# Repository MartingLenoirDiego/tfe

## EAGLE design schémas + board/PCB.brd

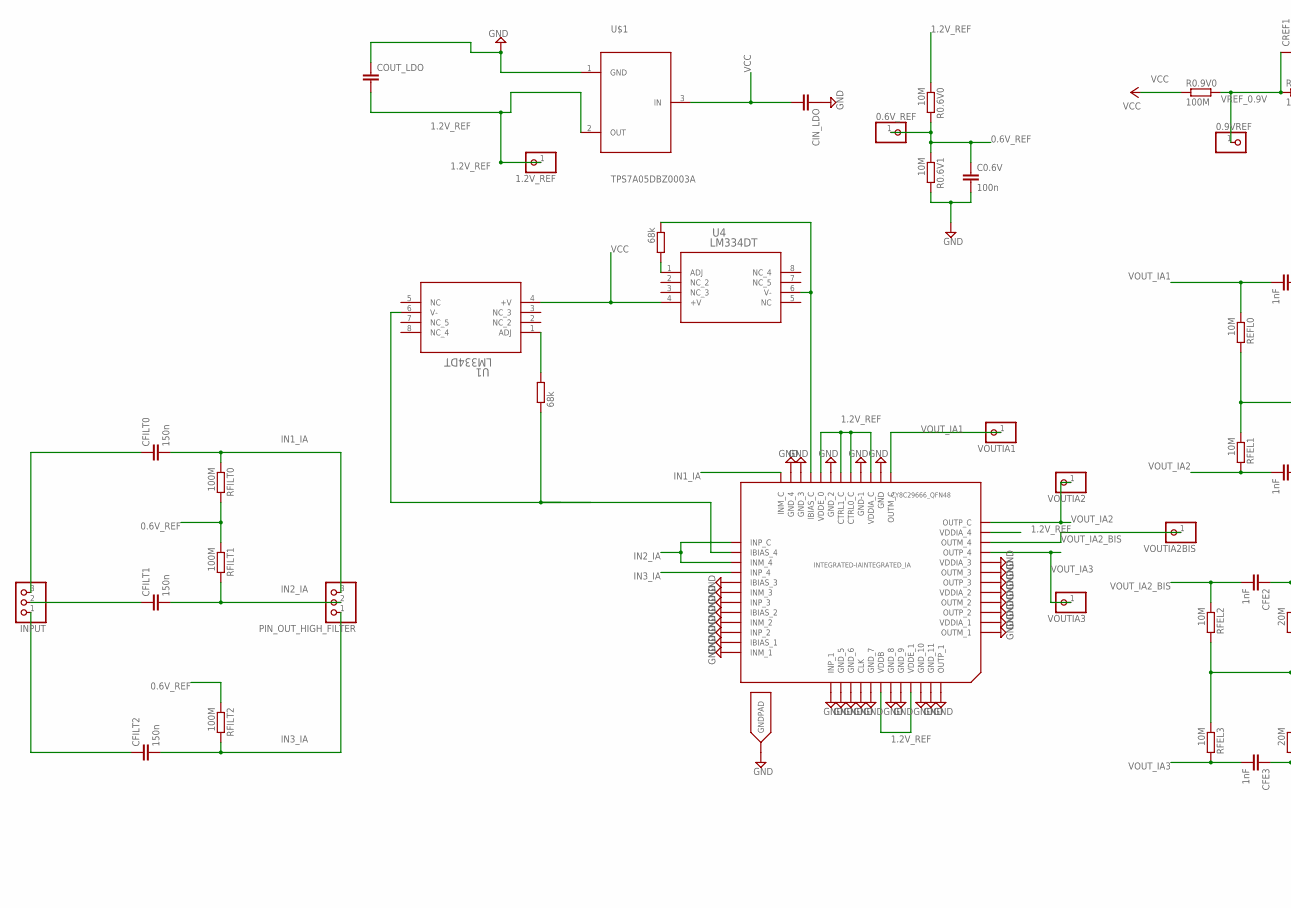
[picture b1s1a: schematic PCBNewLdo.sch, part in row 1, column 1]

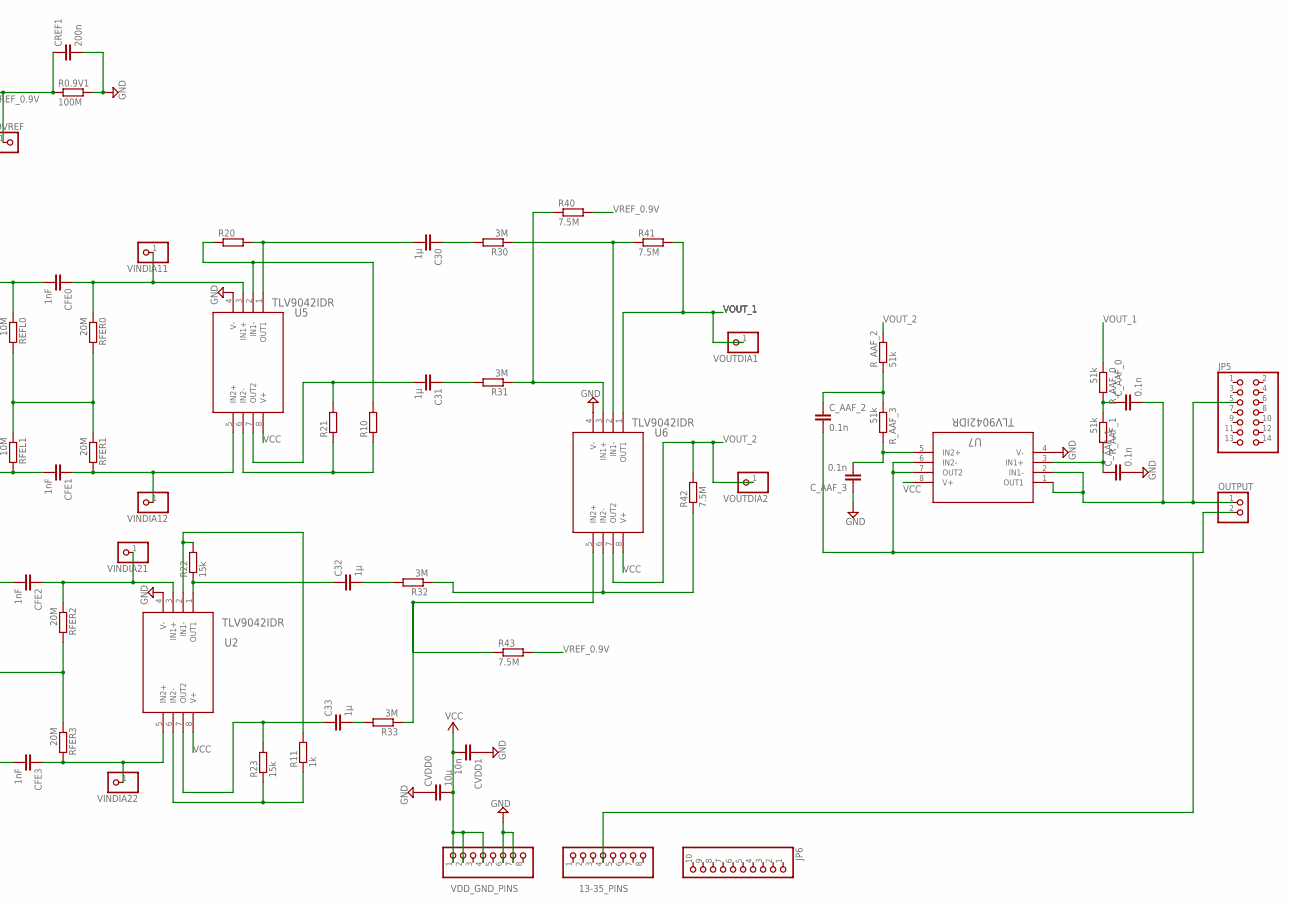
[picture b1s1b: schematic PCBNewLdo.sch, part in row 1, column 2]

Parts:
0.6V_REF, 0.9VREF, 1.2V_REF: PINHD-1X1; 1X01
13-35_PINS: PINHD-1X8; 1X08
C0.6V: 100n; C0603
C30, C31, C32, C33: 1µ; C0603
CFE0, CFE1, CFE2, CFE3: 1nF; C0603
CFILT0, CFILT1, CFILT2: 150n; C0603
CIN_LDO: 1µ; C0603
COUT_LDO: 4.7µ; C0603
CREF1: 200n; C0603
CVDD0: 10µ; C0603
CVDD1: 10n; C0603
C_AAF_0, C_AAF_1, C_AAF_2, C_AAF_3: 0.1n; C0603
INPUT: PINHD-1X3; 1X03
INTEGRATED-IA: CY8C29666_QFN48; QFN48
JP5: PINHD-2X7; 2X07
JP6: PINHD-1X10; 1X10
OUTPUT: PINHD-1X2; 1X02
PIN_OUT_HIGH_FILTER: PINHD-1X3; 1X03
R0.6V0, R0.6V1: 10M; R0603
R0.9V0, R0.9V1: 100M; R0603
R10, R20, R21: R-EU_R0603; R0603
R11: 1k; R0603
R22, R23: 15k; R0603
R30, R31, R32, R33: 3M; R0603
R40, R41, R42, R43: 7.5M; R0603
REFL0: 10M; R0603
RFEL1, RFEL2, RFEL3: 10M; R0603
RFER0, RFER1, RFER2, RFER3: 20M; R0603
RFILT0, RFILT1, RFILT2: 100M; R0603
RLM334_0, RLM334_1: 68k; R0603
R_AAF_0, R_AAF_1, R_AAF_2, R_AAF_3: 51k; R0603
U1, U4: LM334DT; SO-8_STM
U2, U5, U6, U7: TLV9042IDR; SOIC8_D_TEX
U$1: TPS7A05DBZ0003A; TFE
VDD_GND_PINS: PINHD-1X8; 1X08
VINDIA11, VINDIA12, VINDIA21, VINDIA22: PINHD-1X1; 1X01
VOUTDIA1, VOUTDIA2: PINHD-1X1; 1X01
VOUTIA1, VOUTIA2, VOUTIA2BIS, VOUTIA3: PINHD-1X1; 1X01

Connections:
0.6V_REF: 0.6V_REF.1, C0.6V.1, R0.6V0.2, R0.6V1.1, RFILT0.2, RFILT1.1, RFILT2.1
1.2V_REF: 1.2V_REF.1, COUT_LDO.2, INTEGRATED-IA.11 (VDDIA_4), INTEGRATED-IA.15 (VDDIA_C), INTEGRATED-IA.17 (CTRL0_C), INTEGRATED-IA.18 (CTRL1_C), INTEGRATED-IA.20 (VDDE_0), INTEGRATED-IA.42 (VDDB), INTEGRATED-IA.45 (VDDE_1), R0.6V0.1, U$1.2 (OUT); also elsewhere on the board
GND: C0.6V.2, CIN_LDO.1, COUT_LDO.1, CREF1.2, CVDD0.1, CVDD1.1, C_AAF_1.2, C_AAF_3.1, INTEGRATED-IA.1 (OUTM_1), INTEGRATED-IA.2 (VDDIA_1), INTEGRATED-IA.3 (OUTP_2), INTEGRATED-IA.4 (OUTM_2), INTEGRATED-IA.5 (VDDIA_2), INTEGRATED-IA.6 (OUTP_3), INTEGRATED-IA.7 (OUTM_3), INTEGRATED-IA.8 (VDDIA_3), INTEGRATED-IA.14 (GND), INTEGRATED-IA.16 (GND-1), INTEGRATED-IA.19 (GND_2), INTEGRATED-IA.22 (GND_3), INTEGRATED-IA.23 (GND_4), INTEGRATED-IA.29 (IBIAS_3), INTEGRATED-IA.30 (INM_3), INTEGRATED-IA.31 (INP_3), INTEGRATED-IA.32 (IBIAS_2), INTEGRATED-IA.33 (INM_2), INTEGRATED-IA.34 (INP_2), INTEGRATED-IA.35 (IBIAS_1), INTEGRATED-IA.36 (INM_1), INTEGRATED-IA.37 (INP_1), INTEGRATED-IA.38 (GND_5), INTEGRATED-IA.39 (GND_6), INTEGRATED-IA.40 (CLK), INTEGRATED-IA.41 (GND_7), INTEGRATED-IA.43 (GND_8), INTEGRATED-IA.44 (GND_9), INTEGRATED-IA.46 (GND_10), INTEGRATED-IA.47 (GND_11), INTEGRATED-IA.48 (OUTP_1), INTEGRATED-IA.EXP (GNDPAD), R0.6V1.2, R0.9V1.2, U2.4 (V-), U5.4 (V-), U6.4 (V-), U7.4 (V-), U$1.1 (GND), VDD_GND_PINS.6, VDD_GND_PINS.7; also elsewhere on the board
IN1_IA: CFILT0.2, INTEGRATED-IA.24 (INM_C), PIN_OUT_HIGH_FILTER.3, RFILT0.1
IN2_IA: CFILT1.2, INTEGRATED-IA.25 (INP_C), INTEGRATED-IA.27 (INM_4), PIN_OUT_HIGH_FILTER.2, RFILT1.2
IN3_IA: CFILT2.2, INTEGRATED-IA.28 (INP_4), PIN_OUT_HIGH_FILTER.1, RFILT2.2
unnamed: C33.2, R33.2
unnamed: C32.1, R22.1, U2.1 (OUT1)
unnamed: C32.2, R32.2
unnamed: R32.1, R42.1, U6.6 (IN2-)
unnamed: CFILT2.1, INPUT.1
unnamed: R33.1, R43.1, U6.5 (IN2+)
unnamed: REFL0.2, RFEL1.1, RFER0.2, RFER1.1
unnamed: R31.1, R40.1, U6.3 (IN1+)
unnamed: C31.1, R31.2
unnamed: C30.1, R30.2
unnamed: C31.2, R21.2, U5.7 (OUT2)
unnamed: RLM334_1.2, U1.1 (ADJ)
unnamed: CFILT0.1, INPUT.3
unnamed: RLM334_0.2, U4.1 (ADJ)
unnamed: C_AAF_2.1, R_AAF_2.1, R_AAF_3.1
unnamed: C30.2, R20.2, U5.1 (OUT1)
unnamed: C_AAF_0.1, R_AAF_0.2, R_AAF_1.1
unnamed: C_AAF_1.1, R_AAF_1.2, U7.3 (IN1+)
unnamed: C_AAF_3.2, R_AAF_3.2, U7.5 (IN2+)
unnamed: 13-35_PINS.4, C_AAF_2.2, OUTPUT.2, U7.6 (IN2-), U7.7 (OUT2)
unnamed: C_AAF_0.2, JP5.5, OUTPUT.1, U7.1 (OUT1), U7.2 (IN1-)
unnamed: R30.1, R41.1, U6.2 (IN1-)
unnamed: R10.1, R21.1, U5.6 (IN2-)
unnamed: C33.1, R23.2, U2.7 (OUT2)
unnamed: R11.1, R23.1, U2.6 (IN2-)
unnamed: R10.2, R20.1, U5.2 (IN1-)
unnamed: INTEGRATED-IA.26 (IBIAS_4), RLM334_1.1, U1.6 (V-)
unnamed: R11.2, R22.2, U2.2 (IN1-)
unnamed: CFE3.1, RFER3.2, U2.5 (IN2+), VINDIA22.1
unnamed: RFEL2.2, RFEL3.1, RFER2.2, RFER3.1
unnamed: CFE2.1, RFER2.1, U2.3 (IN1+), VINDIA21.1
unnamed: INTEGRATED-IA.21 (IBIAS_C), RLM334_0.1, U4.6 (V-)
unnamed: CFE0.1, RFER0.1, U5.3 (IN1+), VINDIA11.1
unnamed: CFE1.1, RFER1.2, U5.5 (IN2+), VINDIA12.1
unnamed: CFILT1.1, INPUT.2
VCC: CIN_LDO.2, CVDD0.2, CVDD1.2, R0.9V0.1, U1.4 (+V), U2.8 (V+), U4.4 (+V), U5.8 (V+), U6.8 (V+), U7.8 (V+), U$1.3 (IN), VDD_GND_PINS.1, VDD_GND_PINS.2, VDD_GND_PINS.4; also elsewhere on the board
VOUT_1: R41.2, R_AAF_0.1, U6.1 (OUT1), VOUTDIA1.1
VOUT_2: R42.2, R_AAF_2.2, U6.7 (OUT2), VOUTDIA2.1
VOUT_IA1: CFE0.2, INTEGRATED-IA.13 (OUTM_C), REFL0.1, VOUTIA1.1
VOUT_IA2: CFE1.2, INTEGRATED-IA.12 (OUTP_C), RFEL1.2, VOUTIA2.1
VOUT_IA2_BIS: CFE2.2, INTEGRATED-IA.10 (OUTM_4), RFEL2.1, VOUTIA2BIS.1
VOUT_IA3: CFE3.2, INTEGRATED-IA.9 (OUTP_4), RFEL3.2, VOUTIA3.1
VREF_0.9V: 0.9VREF.1, CREF1.1, R0.9V0.2, R0.9V1.1, R40.2, R43.2

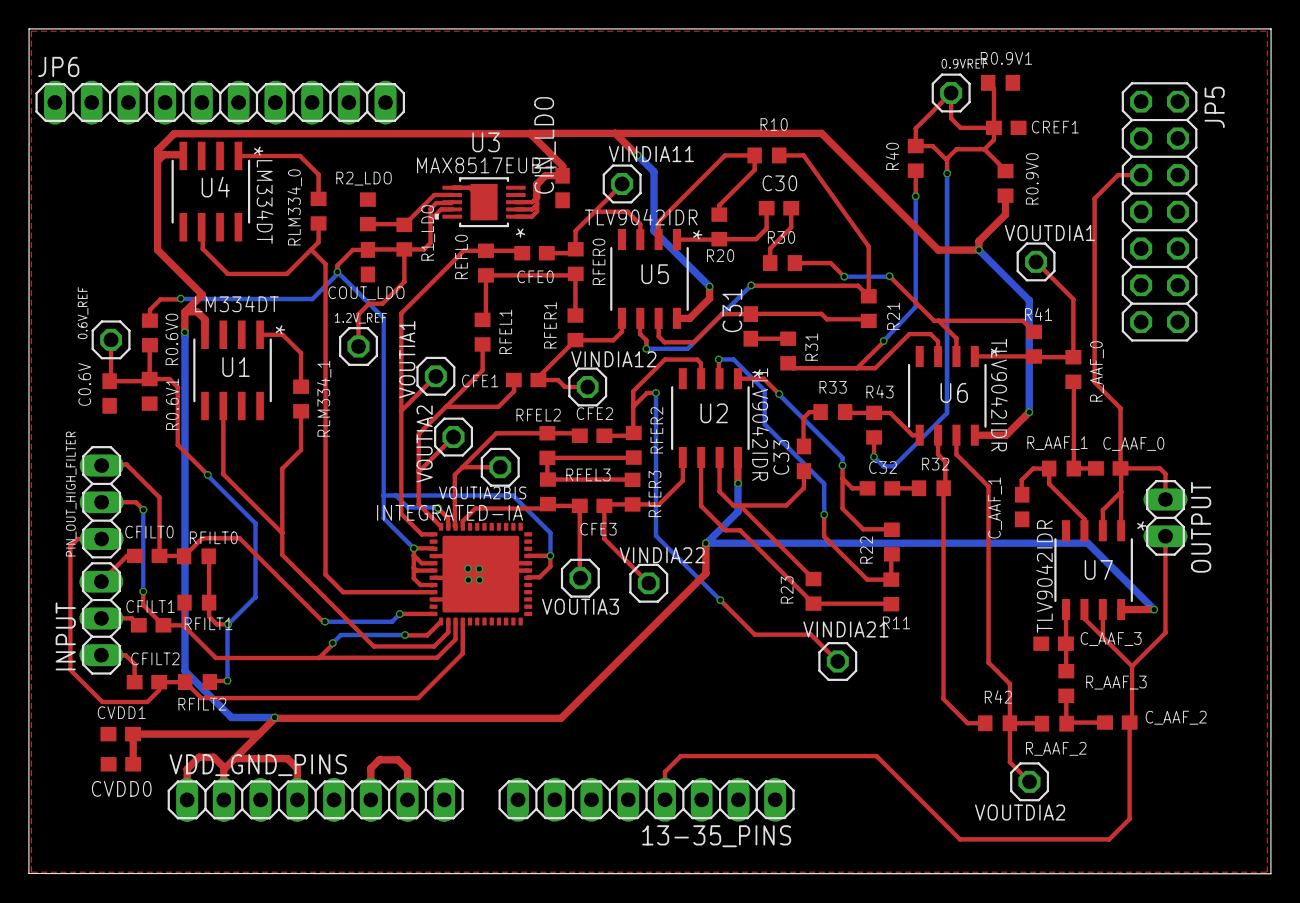
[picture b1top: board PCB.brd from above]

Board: 2 copper layers, 85.9 x 58.4 mm, 86 parts (0 on the bottom side), 50 nets.

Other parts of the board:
R1_LDO: 280k; R0603
R2_LDO: 200k; R0603
U3: MAX8517EUB+; 21-0109D_MXM

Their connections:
1.2V_REF: R1_LDO.2, U3.8, U3.9; also elsewhere on the board
GND: R2_LDO.2, U3.6, U3.EPAD; also elsewhere on the board
unnamed: R1_LDO.1, R2_LDO.1, U3.7
VCC: U3.1, U3.2, U3.3; also elsewhere on the board

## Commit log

2022-03-17 arborescence
2022-03-30 mise à jour bom
2022-05-09 last
2022-05-09 code transfert uart
2022-05-23 code uart adc
2022-05-23 test
2022-06-02 code python + apollo
2022-06-02 modif structure
2022-06-03 rapport
2022-06-04 finalisation message erreur
2022-06-05 modif

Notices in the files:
parts and their libraries:
COPYRIGHT: Copyright (C) 2018 Accelerated Designs. All rights reserved
